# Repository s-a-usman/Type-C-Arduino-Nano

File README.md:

# Arduino-nano-with-type_C

This is an Arduino nano board with type c port instead of the popular type b.

## Acknowledgement

The original project was downloaded from (Arduino Official Store)[https://store.arduino.cc/products/arduino-nano].

3D models in the [NanoV3.3.3dshapes](NanoV3.3.3dshapes) directory are works of others.

| File | Source |
| ---- | ------ |
| DO-220AA.stp | https://componentsearchengine.com/part-view/SS1P3L-M3%2F84A/Vishay |
| SW_SPST_3.9x2.9mm.wrl | https://lceda.cn |
| Others | https://gitlab.com/kicad/libraries/kicad-packages3D |

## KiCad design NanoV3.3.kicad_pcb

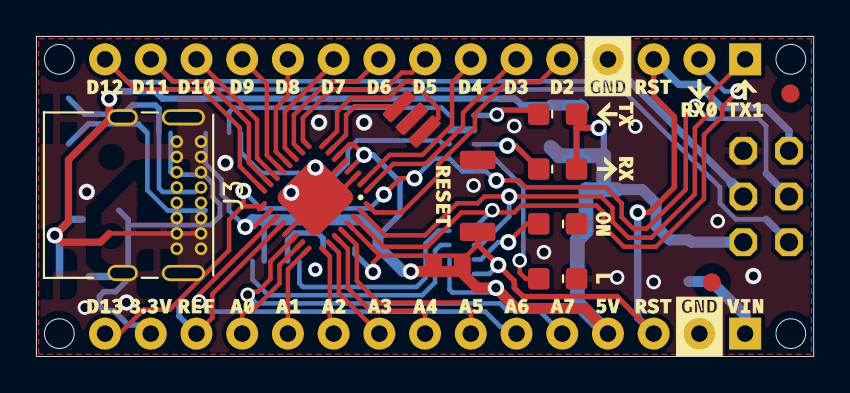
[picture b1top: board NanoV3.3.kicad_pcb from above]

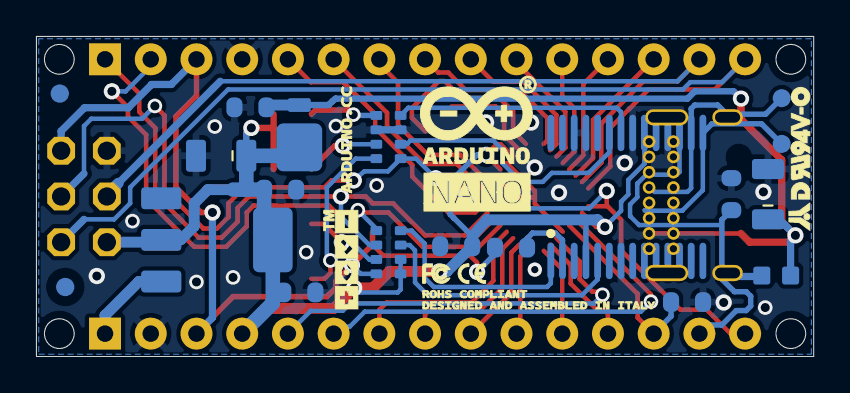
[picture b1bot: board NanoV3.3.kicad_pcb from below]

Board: 2 copper layers, 43.2 x 17.8 mm, 35 parts (20 on the bottom side), 37 nets.

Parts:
C1, C4, C6, C9: 100nF; C_0603_1608Metric
C2, C5: 4,7uF_16V; CP_EIA-3216-18_Kemet-A
C3, C7, C8: 1uF; C_0603_1608Metric
D1: SS1P3L; DO-220AA
D+0: DNP; TestPoint_Pad_D1.0mm
D-0: DNP; TestPoint_Pad_D1.0mm
F1, F1#2: MFFSMF050; Fuse_0603_1608Metric
FD1, FD2, FD3, FD4: DNP; Fiducial_1mm_Mask1.5mm
IC1: FT232RL; SSOP-28_5.3x10.2mm_P0.65mm
IC2: LM1117IMPX-5.0; SOT-223
IC3: 328P-MUR; VQFN-32-1EP_5x5mm_P0.5mm_EP3.254x3.254mm
J1, J2: Conn_1x15; PinHeader_1x15_P2.54mm_Vertical
J3: USB_2; USB_C_Receptacle_GCT_USB4085
J4: Conn_2x3; PinHeader_2x3_P2.54mm_Vertical
L0: Yellow; LED_0805_2012Metric
PWR0: Green; LED_0805_2012Metric
RP1, RP2: 1K; R_CAY16-4
RX0: Red; LED_0805_2012Metric
SW1: RESET; SW_SPST_3.9x2.9mm
Silkscreen_Back: Silkscreen_Front; Silkscreen_Back
Silkscreen_Front: Silkscreen_Back; Silkscreen_Front
TX0: Green; LED_0805_2012Metric
Y1: 16MHz; Resonator_SMD_Murata_CSTxExxV-3Pin_3.0x1.1mm

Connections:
/A0: IC3.23 (PC0(ADC0)), J2.12
/A1: IC3.24 (PC1(ADC1)), J2.11
/A2: IC3.25 (PC2(ADC2)), J2.10
/A3: IC3.26 (PC3(ADC3)), J2.9
/A4: IC3.27 (PC4(ADC4/SDA)), J2.8
/A5: IC3.28 (PC5(ADC5/SCL)), J2.7
/A6: IC3.19 (ADC6), J2.6
/A7: IC3.22 (ADC7), J2.5
/AREF: C1.1, IC3.20 (AREF), J2.13
/D0/RX: IC3.30 (PD0(RXD)), J1.2, RP1.1
/D1/TX: IC3.31 (PD1(TXD)), J1.1, RP1.2 (1)
/D2: IC3.32 (PD2(INT0)), J1.5
/D3: IC3.1 (PD3(INT1)), J1.6
/D4: IC3.2 (PD4(XCK/T0)), J1.7
/D5: IC3.9 (PD5(T1)), J1.8
/D6: IC3.10 (PD6(AIN0)), J1.9
/D7: IC3.11 (PD7(AIN1)), J1.10
/D8: IC3.12 (PB0(ICP)), J1.11
/D9: IC3.13 (PB1(OC1A)), J1.12
/D10: IC3.14 (PB2(SS/OC1B)), J1.13
/D11/MOSI: IC3.15 (PB3(MOSI/OC2)), J1.14, J4.4
/D12/MISO: IC3.16 (PB4(MISO)), J1.15, J4.1
/D13/SCK: IC3.17 (PB5(SCK)), J2.15, J4.3, RP2.1
/RX: IC1.1 (TXD), RP1.8 (2)
/TX: IC1.5 (RXD), RP1.7 (2)
COM: C1.2, C2.2 (-), C3.2, C5.2 (-), C6.1, C7.2, C8.2, C9.2, IC1.7 (GND1), IC1.21 (GND3), IC1.25 (AGND), IC1.26 (TEST), IC2.1 (GND/ADJ), IC3.3 (GND), IC3.5 (GND), IC3.21 (AGND), IC3.33 (GND), J1.4, J2.2, J3.A12 (GND), J3.B1 (GND), J3.S1 (SHIELD), J4.6, L0.2, PWR0.2, RP2.3 (1), RP2.6 (2), SW1.1, Y1.2
unnamed: IC1.23 (CBUS0), RP2.2 (1)
unnamed: IC1.22 (CBUS1), RP2.4 (1)
unnamed: C4.2, IC1.2 (DTR#)
unnamed: IC3.7 (PB6(XTAL1/TOSC1)), Y1.1
unnamed: IC3.8 (PB7(XTAL2/TOSC2)), Y1.3
unnamed: C2.1 (+), C3.1, C4.1, C5.1 (+), C6.2, C7.1, C8.1, C9.1, D1.1 (K), D1.2 (A), D+0.X, D-0.X, F1.1, F1.2, F1#2.1, F1#2.2, IC1.4 (VCCIO), IC1.15 (USBDP), IC1.16 (USBDM), IC1.17 (3V3OUT), IC1.18 (GND2), IC1.19 (RESET#), IC1.20 (VCC), IC2.2, IC2.4 (OUT), IC3.4 (VCC), IC3.6 (VCC), IC3.18 (AVCC), IC3.29 (PC6(/RESET)), J1.3, J2.3, J2.4, J2.14, J3.A1 (GND), J3.A4 (VBUS), J3.A5 (CC1), J3.A6 (D+), J3.A7 (D-), J3.A8 (SBU1), J3.A9 (VBUS), J3.B4 (VBUS), J3.B5 (CC2), J3.B6 (D+), J3.B7 (D-), J3.B8 (SBU2), J3.B9 (VBUS), J3.B12 (GND), J3.S1 (SHIELD), J4.2, J4.5, RP1.4 (1), RP1.5 (2), RP1.6 (2), RX0.1, SW1.2, TX0.1
unnamed: PWR0.1, RP1.3 (1)
unnamed: L0.1, RP2.8 (2)
unnamed: RP2.7 (2), RX0.2
unnamed: RP2.5 (2), TX0.2
VIN: IC2.3 (IN), J2.1

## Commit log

2023-12-20 Add design files
